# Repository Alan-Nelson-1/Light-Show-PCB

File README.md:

# Light-Show-PCB
This includes the schematic, pcb files as well as the KiCAD project file for the PCB created for conrolling a high current load using N channel MOSFETs (IRZ44N)
for fast switching speeds.

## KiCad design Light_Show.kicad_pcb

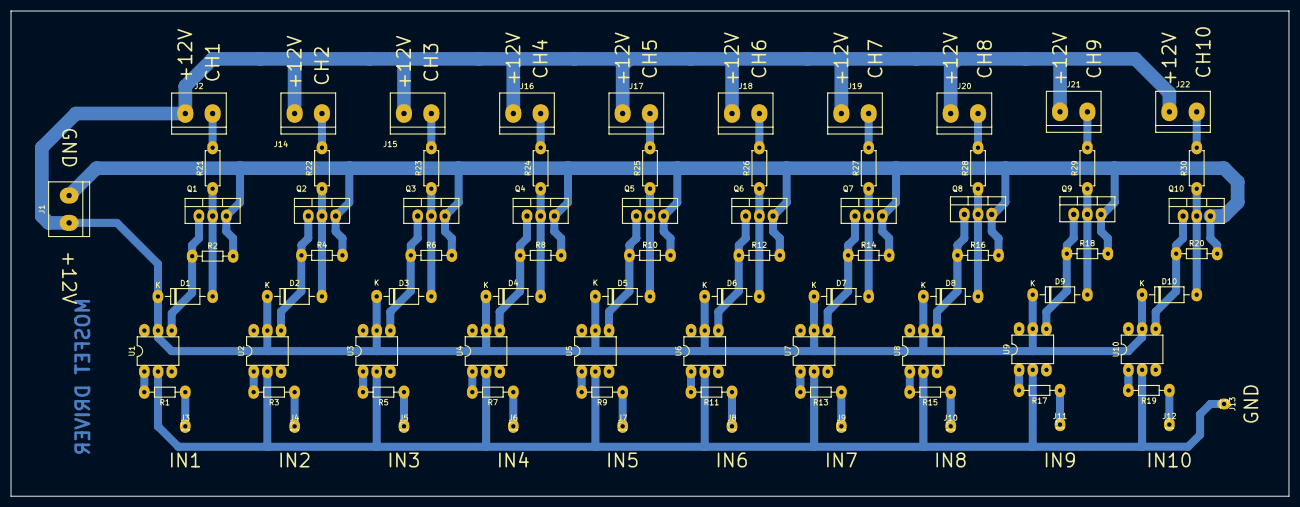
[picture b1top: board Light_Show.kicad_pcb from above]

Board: 2 copper layers, 237.5 x 90.2 mm, 82 parts (0 on the bottom side), 53 nets.

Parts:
D1, D2, D3, D4, D5, D6, D7, D8, D9, D10: 1N4007; D_DO-41_SOD81_P10.16mm_Horizontal
J1, J2, J14, J15, J16, J17, J18, J19, J20, J21, J22: Screw_Terminal_01x02; TerminalBlock_bornier-2_P5.08mm
J3, J4, J5, J6, J7, J8, J9, J10, J11, J12, J13: Conn_01x01_Male; PinHeader_1x01_P1.00mm_Vertical
Q1, Q2, Q3, Q4, Q5, Q6, Q7, Q8, Q9, Q10: IRLZ44N; TO-220-3_Vertical
R1, R2, R3, R4, R5, R6, R7, R8, R9, R10, R11, R12, R13, R14, R15, R16, R17, R18, R19, R20: R_US; R_Axial_DIN0204_L3.6mm_D1.6mm_P7.62mm_Horizontal
R21, R22, R23, R24, R25, R26, R27, R28, R29, R30: R_US; R_Axial_DIN0207_L6.3mm_D2.5mm_P7.62mm_Horizontal
U1, U2, U3, U4, U5, U6, U7, U8, U9, U10: 4N25; DIP-6_W7.62mm

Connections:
unnamed: D1.1 (K), D2.1 (K), D3.1 (K), D4.1 (K), D5.1 (K), D6.1 (K), D7.1 (K), D8.1 (K), D9.1 (K), D10.1 (K), J1.1, J2.1, J14.1, J15.1, J16.1, J17.1, J18.1, J19.1, J20.1, J21.1, J22.1, U1.5, U2.2, U3.5, U4.5, U5.5, U6.5, U7.5, U8.5, U9.5, U10.5
unnamed: D1.2 (A), Q1.2 (D), R21.1
unnamed: D2.2 (A), Q2.2 (D), R22.1
unnamed: D3.2 (A), Q3.2 (D), R23.1
unnamed: D4.2 (A), Q4.2 (D), R24.1
unnamed: D5.2 (A), Q5.2 (D), R25.1
unnamed: D6.2 (A), Q6.2 (D), R26.1
unnamed: D7.2 (A), Q7.2 (D), R27.1
unnamed: D8.2 (A), Q8.2 (D), R28.1
unnamed: D9.2 (A), Q9.2 (D), R29.1
unnamed: D10.2 (A), Q10.2 (D), R30.1
unnamed: J1.2, Q1.3 (S), Q2.3 (S), Q3.3 (S), Q4.3 (S), Q5.3 (S), Q6.3 (S), Q7.3 (S), Q8.3 (S), Q9.3 (S), Q10.3 (S), R2.2, R4.2, R6.2, R8.2, R10.2, R12.2, R14.2, R16.2, R18.2, R20.2
unnamed: J2.2, R21.2
unnamed: J3.1, R1.1
unnamed: J4.1, R3.1
unnamed: J5.1, R5.1
unnamed: J6.1, R7.1
unnamed: J7.1, R9.1
unnamed: J8.1, R11.1
unnamed: J9.1, R13.1
unnamed: J10.1, R15.1
unnamed: J11.1, R17.1
unnamed: J12.1, R19.1
unnamed: J13.1, U1.2, U2.2, U3.2, U4.2, U5.2, U6.2, U7.2, U8.2, U9.2, U10.2
unnamed: J14.2, R22.2
unnamed: J15.2, R23.2
unnamed: J16.2, R24.2
unnamed: J17.2, R25.2
unnamed: J18.2, R26.2
unnamed: J19.2, R27.2
unnamed: J20.2, R28.2
unnamed: J21.2, R29.2
unnamed: J22.2, R30.2
unnamed: Q1.1 (G), R2.1, U1.4
unnamed: Q2.1 (G), R4.1, U2.4
unnamed: Q3.1 (G), R6.2, U3.4
unnamed: Q4.1 (G), R8.1, U4.4
unnamed: Q5.1 (G), R10.1, U5.4
unnamed: Q6.1 (G), R12.1, U6.4
unnamed: Q7.1 (G), R14.1, U7.4
unnamed: Q8.1 (G), R16.1, U8.4
unnamed: Q9.1 (G), R18.1, U9.4
unnamed: Q10.1 (G), R20.1, U10.4
unnamed: R1.2, U1.1
unnamed: R3.2, U2.1
unnamed: R5.2, U3.1
unnamed: R7.2, U4.1
unnamed: R9.2, U5.1
unnamed: R11.2, U6.1
unnamed: R13.2, U7.1
unnamed: R15.2, U8.1
unnamed: R17.2, U9.1
unnamed: R19.2, U10.1
